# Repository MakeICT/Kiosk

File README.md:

# Kiosk
A kiosk to automate cash payments and other stuff

# Hardware
* NCR 5965-1014-9090 Touchscreen Monitor
* Dell Optiplex 755 Desktop
* Coinco Mag50B Bill Acceptor
* CH926 Coin Acceptor
* Arduino Nano

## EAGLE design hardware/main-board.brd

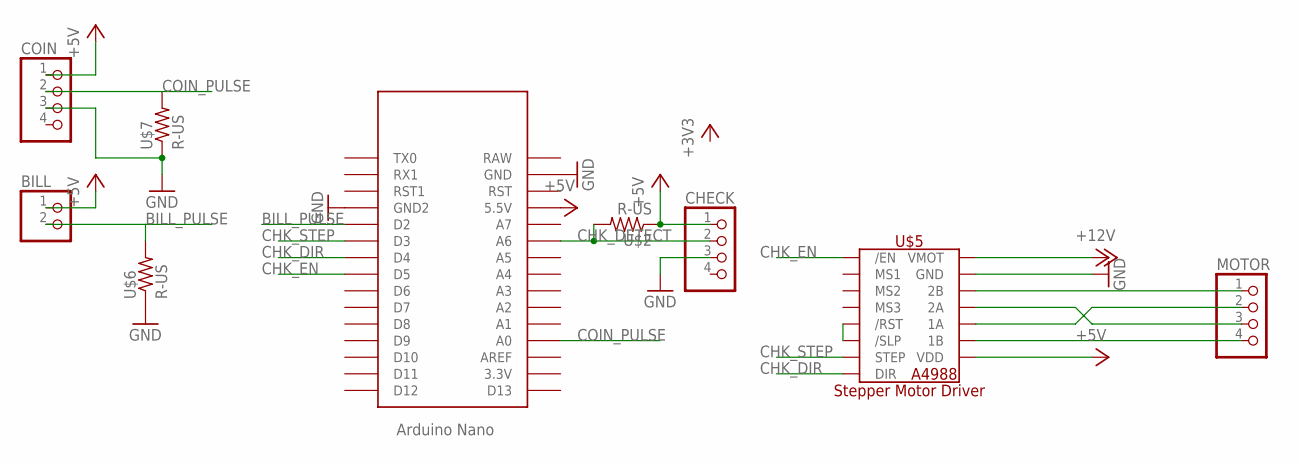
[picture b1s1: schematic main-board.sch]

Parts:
BILL: PINHD-1X2; 1X02
CHECK: PINHD-1X4; 1X04
COIN: PINHD-1X4; 1X04
MOTOR: PINHD-1X4; 1X04
U$1: NANO
U$2, U$6, U$7: R-US; 0204/7
U$5: A4988_STEP

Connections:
+5V: BILL.1, CHECK.1, COIN.1, U$1.5V (5.5V), U$2.1, U$5.VDD
+12V: U$5.VMOT
BILL_PULSE: BILL.2, U$1.D2, U$6.2
CHK_DETECT: CHECK.2, U$1.A6, U$2.2
CHK_DIR: U$1.D4, U$5.DIR
CHK_EN: U$1.D5, U$5./EN
CHK_STEP: U$1.D3, U$5.STEP
COIN_PULSE: COIN.2, U$1.A0, U$7.2
GND: CHECK.3, COIN.3, U$1.GND, U$1.GND1 (GND2), U$5.GND, U$5.GND2 (GND), U$6.1, U$7.1
unnamed: MOTOR.2, U$5.1A
unnamed: MOTOR.3, U$5.2A
unnamed: MOTOR.1, U$5.2B
unnamed: MOTOR.4, U$5.1B
unnamed: U$5./RST, U$5./SLP

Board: 2 copper layers, 9 parts (0 on the bottom side), 13 nets, no tracks yet.

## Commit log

2019-01-15 add touchscreen drivers, setup script, and some api libraries
2019-01-17 Improve setup script
2019-01-17 add placeholder html file for UI
2019-01-17 fix erro in setup script, delete old files when setup is run
2019-01-17 fix format of echo command in setup script
2019-01-21 start work on basic UI and login screen
2019-01-21 add command to disable gnome keyring
2019-02-10 change logo color, add scan badge page
2019-03-20 add arduino firmware file and test files
2019-03-20 add coin acceptor model to readme
2019-05-15 add base flask files
2019-06-02 add sketch to test check slot
2019-09-25 add schematic from main board
2019-10-08 fix board layout - motor outputs corrected - pullup resistor corrected on coin acceptor
2019-10-08 fix coin test firmware - pulse tracking was inverted - change pulse value to 1 cent
